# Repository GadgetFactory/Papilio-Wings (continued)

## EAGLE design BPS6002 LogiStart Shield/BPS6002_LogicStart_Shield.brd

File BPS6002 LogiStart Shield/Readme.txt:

BPS6002 LogicStart Shield Manufacturing Package - Current Version 1.02

Special assembly instructions:
	-Use RED for the PCB color.
	-All Arduino Mega Header pins should be populated with Male headers on the bottom of the board.
	-There is a V-Score indicated on the dimension layer of this PCB. The board should be manufactured as a single PCB with both sides of the V-Score connected. The end user will snap away the V-Score if they wish to do so.

Test Plan Home Page:
	http://www.gadgetfactory.net/opmanuals/index.php?n=Main.LogicStartShield

3D Rendering Video:
https://www.youtube.com/watch?v=OsVe8Iz7Yxw
	
CHANGELOG
11/18/2014	Version 1.02
	-Moved the Audio jack out for easier manufacturing.

10/22/2014	Version 1.01
	-R48-R52 were not in the BOM for 1.0, added for 1.01
	-The Seven Segment Display must be a Common Anode type display - the prototypes used Common Cathode which do not work.
	-Changed the Analog voltage from 5V to 3.3V
	-Added AREF access point.

8/12/2014 	Version 1.0
	First release with V-Score.

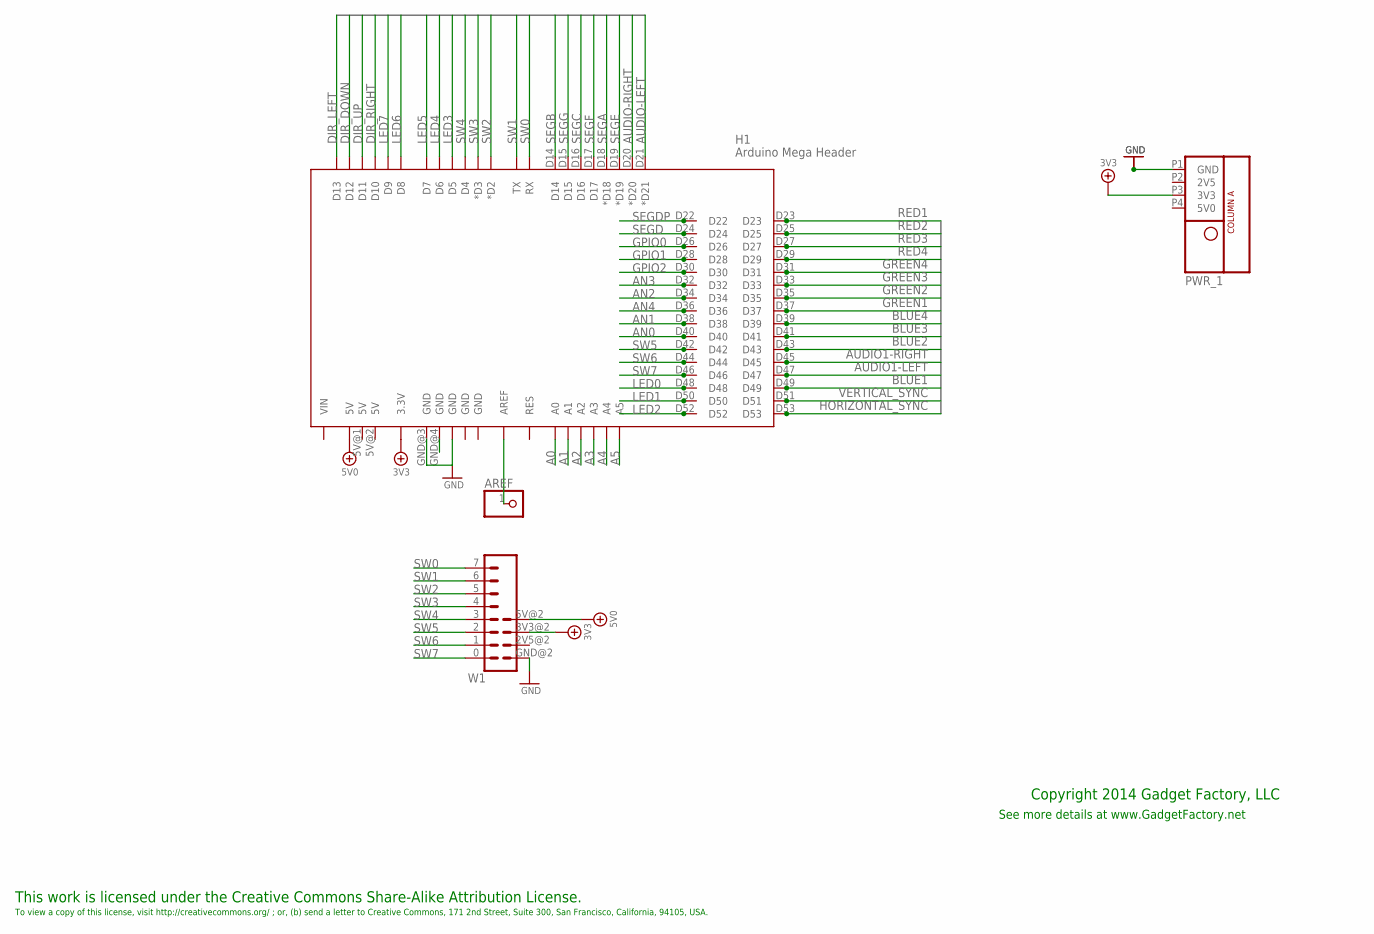
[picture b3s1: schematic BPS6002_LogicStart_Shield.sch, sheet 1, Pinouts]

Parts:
AREF: PINHD-1X1; 1X01
H1: Arduino Mega Header; PAPILIO_DUO_SHIELD; PARTNO 65PinHeader
LOGO1: BUTTERFLY_LOGO
PWR_1: POWER_ONLYNOTEXT; POWER_NO_TEXT
W1: WING8_NOHOLES_FEMALE_TOP; WINGSIDE_8BIT_NOHOLES

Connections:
3V3: H1.3.3V, W1.3V3@2 (3V3); also elsewhere on the board
5V0: H1.5V@0 (5V), W1.5V@2 (5V)
A0: H1.A0; also elsewhere on the board
A1: H1.A1; also elsewhere on the board
A2: H1.A2; also elsewhere on the board
A3: H1.A3; also elsewhere on the board
A4: H1.A4; also elsewhere on the board
A5: H1.A5; also elsewhere on the board
AN0: H1.D40; also elsewhere on the board
AN1: H1.D38; also elsewhere on the board
AN2: H1.D34; also elsewhere on the board
AN3: H1.D32; also elsewhere on the board
AN4: H1.D36; also elsewhere on the board
AUDIO1-LEFT: H1.D47
AUDIO1-RIGHT: H1.D45
AUDIO-LEFT: H1.D21 (*D21); also elsewhere on the board
AUDIO-RIGHT: H1.D20 (*D20); also elsewhere on the board
BLUE1: H1.D49; also elsewhere on the board
BLUE2: H1.D43; also elsewhere on the board
BLUE3: H1.D41; also elsewhere on the board
BLUE4: H1.D39; also elsewhere on the board
DIR_DOWN: H1.D12; also elsewhere on the board
DIR_LEFT: H1.D13; also elsewhere on the board
DIR_RIGHT: H1.D10; also elsewhere on the board
DIR_UP: H1.D11; also elsewhere on the board
GND: H1.GND@2 (GND), H1.GND@3 (GND), W1.GND@2 (GND); also elsewhere on the board
GPIO0: H1.D26; also elsewhere on the board
GPIO1: H1.D28; also elsewhere on the board
GPIO2: H1.D30; also elsewhere on the board
GREEN1: H1.D37; also elsewhere on the board
GREEN2: H1.D35; also elsewhere on the board
GREEN3: H1.D33; also elsewhere on the board
GREEN4: H1.D31; also elsewhere on the board
HORIZONTAL_SYNC: H1.D53; also elsewhere on the board
LED0: H1.D48; also elsewhere on the board
LED1: H1.D50; also elsewhere on the board
LED2: H1.D52; also elsewhere on the board
LED3: H1.D5; also elsewhere on the board
LED4: H1.D6; also elsewhere on the board
LED5: H1.D7; also elsewhere on the board
LED6: H1.D8; also elsewhere on the board
LED7: H1.D9; also elsewhere on the board
unnamed: AREF.1, H1.AREF
RED1: H1.D23; also elsewhere on the board
RED2: H1.D25; also elsewhere on the board
RED3: H1.D27; also elsewhere on the board
RED4: H1.D29; also elsewhere on the board
SEGA: H1.D18 (*D18); also elsewhere on the board
SEGB: H1.D14; also elsewhere on the board
SEGC: H1.D16; also elsewhere on the board
SEGD: H1.D24; also elsewhere on the board
SEGDP: H1.D22; also elsewhere on the board
SEGE: H1.D19 (*D19); also elsewhere on the board
SEGF: H1.D17; also elsewhere on the board
SEGG: H1.D15; also elsewhere on the board
SW0: H1.RX, W1.7 (8); also elsewhere on the board
SW1: H1.TX, W1.6 (7); also elsewhere on the board
SW2: H1.D2 (*D2), W1.5 (6); also elsewhere on the board
SW3: H1.D3 (*D3), W1.4 (5); also elsewhere on the board
SW4: H1.D4, W1.3 (4); also elsewhere on the board
SW5: H1.D42, W1.2 (3); also elsewhere on the board
SW6: H1.D44, W1.1 (2); also elsewhere on the board
SW7: H1.D46, W1.0 (1); also elsewhere on the board
VERTICAL_SYNC: H1.D51; also elsewhere on the board
WING_3V3: PWR_1.P3 (3V3)
WING_GND: H1.GND@4 (GND), PWR_1.P1 (GND); also elsewhere on the board

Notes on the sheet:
This work is licensed under the Creative Commons Share-Alike Attribution License.
To view a copy of this license, visit http://creativecommons.org/ ; or, (b) send a letter to Creative Commons, 171 2nd Street, Suite 300, San Francisco, California, 94105, USA.
Copyright 2014 Gadget Factory, LLC
See more details at www.GadgetFactory.net

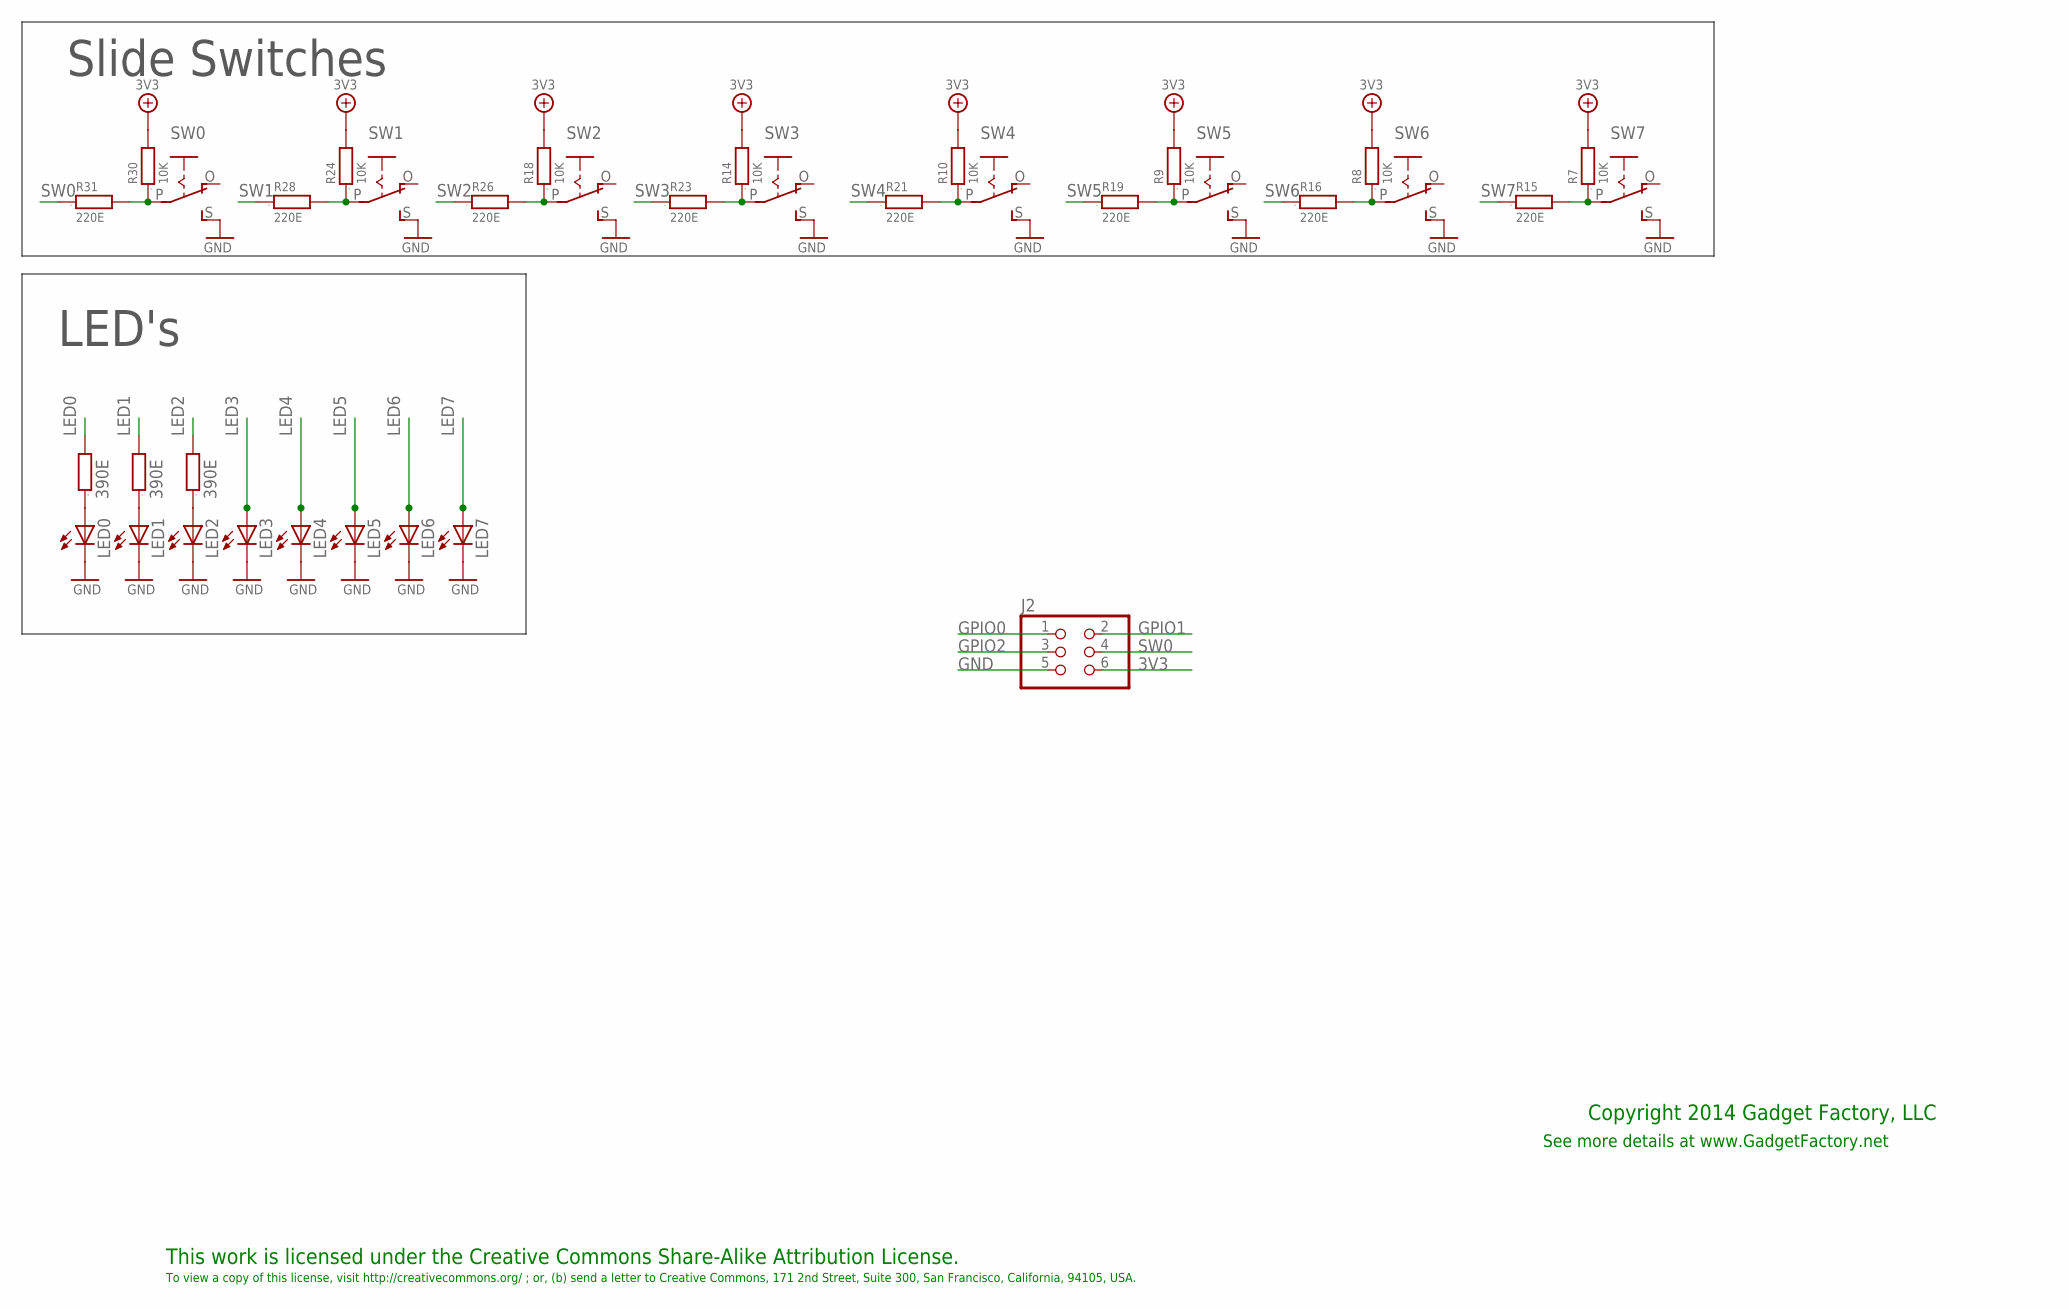
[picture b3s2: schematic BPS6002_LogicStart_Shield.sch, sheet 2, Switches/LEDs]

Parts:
J2: PINHD-2X3; 2X03
LED0, LED1, LED2, LED3, LED4, LED5, LED6, LED7: LEDCHIPLED_0805; CHIPLED_0805; PARTNO LTST-C170KGKT
R7, R8, R9, R10, R14, R18, R24, R30: 10K; 0603; PARTNO RMCF0603JT10K0
R11, R12, R13: 390E; 0603; PARTNO RMCF0603JT390R
R15, R16, R19, R21, R23, R26, R28, R31: 220E; 0603; PARTNO RMCF0603JT220R
SW0, SW1, SW2, SW3, SW4, SW5, SW6, SW7: EG1218S; EG1218; PARTNO EG1218

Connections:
3V3: J2.6, R7.2, R8.2, R9.2, R10.2, R14.2, R18.2, R24.2, R30.2; also elsewhere on the board
GND: J2.5, LED0.C, LED1.C, LED2.C, LED3.C, LED4.C, LED5.C, LED6.C, LED7.C, SW0.S, SW1.S, SW2.S, SW3.S, SW4.S, SW5.S, SW6.S, SW7.S; also elsewhere on the board
GPIO0: J2.1; also elsewhere on the board
GPIO1: J2.2; also elsewhere on the board
GPIO2: J2.3; also elsewhere on the board
LED0: R13.2; also elsewhere on the board
LED1: R12.2; also elsewhere on the board
LED2: R11.2; also elsewhere on the board
LED3: LED3.A; also elsewhere on the board
LED4: LED4.A; also elsewhere on the board
LED5: LED5.A; also elsewhere on the board
LED6: LED6.A; also elsewhere on the board
LED7: LED7.A; also elsewhere on the board
unnamed: LED0.A, R13.1
unnamed: LED1.A, R12.1
unnamed: LED2.A, R11.1
SW0: J2.4, R31.1; also elsewhere on the board
SW0_JOY_UP_IN: R30.1, R31.2, SW0.P
SW1: R28.1; also elsewhere on the board
SW1__JOY_DOWN_IN: R24.1, R28.2, SW1.P
SW2: R26.1; also elsewhere on the board
SW2_JOY_SELECT_IN: R18.1, R26.2, SW2.P
SW3: R23.1; also elsewhere on the board
SW3_JOY_RIGHT_IN: R14.1, R23.2, SW3.P
SW4: R21.1; also elsewhere on the board
SW4_JOY_LEFT_IN: R10.1, R21.2, SW4.P
SW5: R19.1; also elsewhere on the board
SW5_IN: R9.1, R19.2, SW5.P
SW6: R16.1; also elsewhere on the board
SW6_IN: R8.1, R16.2, SW6.P
SW7: R15.1; also elsewhere on the board
SW7_IN: R7.1, R15.2, SW7.P

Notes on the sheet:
This work is licensed under the Creative Commons Share-Alike Attribution License.
To view a copy of this license, visit http://creativecommons.org/ ; or, (b) send a letter to Creative Commons, 171 2nd Street, Suite 300, San Francisco, California, 94105, USA.
Copyright 2014 Gadget Factory, LLC
See more details at www.GadgetFactory.net
LED's
Slide Switches

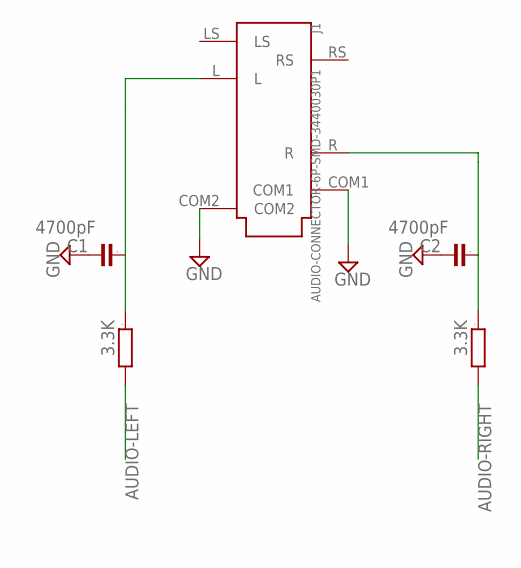
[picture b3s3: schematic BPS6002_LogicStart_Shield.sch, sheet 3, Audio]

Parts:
C1, C2: 4700pF; 0603; PARTNO C0603C472J5RACTU
J1: AUDIO-CONNECTOR-6P-SMD-3440030P1; 6P-SMD-3.5; PARTNO 3440030P1
R2, R3: 3.3K; 0603; PARTNO RMCF0603JT3K30

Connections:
AUDIO-LEFT: R2.2; also elsewhere on the board
AUDIO-RIGHT: R3.2; also elsewhere on the board
GND: C1.2, C2.2, J1.COM1, J1.COM2; also elsewhere on the board
unnamed: C1.1, J1.L, R2.1
unnamed: C2.1, J1.R, R3.1

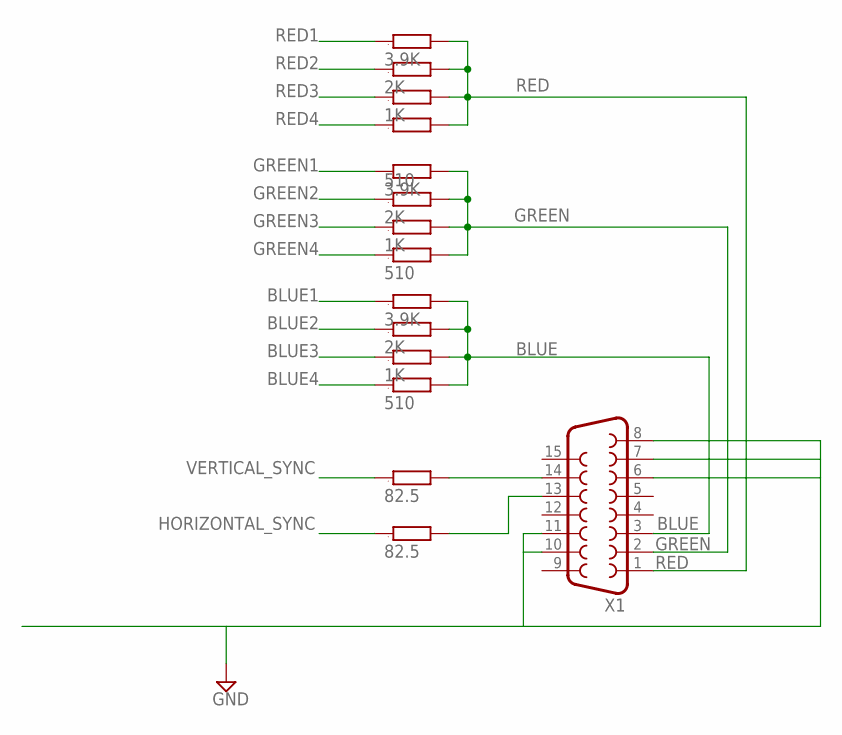
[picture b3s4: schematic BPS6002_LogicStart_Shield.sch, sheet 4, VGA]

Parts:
R34, R41, R45: 3.9K; 0603; PARTNO RMCF0603JT3K90
R35, R40, R44: 2K; 0603; PARTNO RMCF0603JT2K00
R36, R39, R43: 1K; 0603; PARTNO RMCF0603JT1K00
R37, R38, R42: 510; 0603; PARTNO RMCF0603JT510R
R46, R47: 82.5; 0603; PARTNO RMCF0603FT82R5
X1: F15HDH; HDF15H; PARTNO 1-1734530-1

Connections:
BLUE: R42.2, R43.2, R44.2, R45.2, X1.3
BLUE1: R45.1; also elsewhere on the board
BLUE2: R44.1; also elsewhere on the board
BLUE3: R43.1; also elsewhere on the board
BLUE4: R42.1; also elsewhere on the board
GREEN: R38.2, R39.2, R40.2, R41.2, X1.2
GREEN1: R41.1; also elsewhere on the board
GREEN2: R40.1; also elsewhere on the board
GREEN3: R39.1; also elsewhere on the board
GREEN4: R38.1; also elsewhere on the board
HORIZONTAL_SYNC: R47.1; also elsewhere on the board
unnamed: R47.2, X1.13
unnamed: R46.2, X1.14
RED: R34.2, R35.2, R36.2, R37.2, X1.1
RED1: R34.1; also elsewhere on the board
RED2: R35.1; also elsewhere on the board
RED3: R36.1; also elsewhere on the board
RED4: R37.1; also elsewhere on the board
VERTICAL_SYNC: R46.1; also elsewhere on the board
WING_GND: X1.6, X1.7, X1.8, X1.10, X1.11; also elsewhere on the board

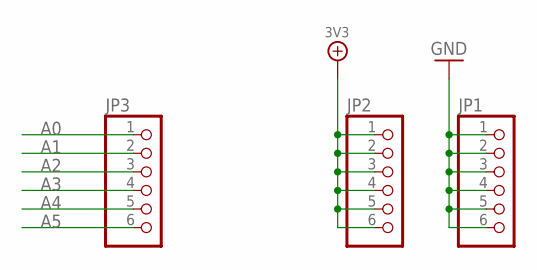
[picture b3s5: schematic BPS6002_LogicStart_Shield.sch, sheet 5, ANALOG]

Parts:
JP1, JP2, JP3: PINHD-1X6; 1X06; PARTNO 68000-406HLF

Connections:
3V3: JP2.1, JP2.2, JP2.3, JP2.4, JP2.5, JP2.6; also elsewhere on the board
A0: JP3.1; also elsewhere on the board
A1: JP3.2; also elsewhere on the board
A2: JP3.3; also elsewhere on the board
A3: JP3.4; also elsewhere on the board
A4: JP3.5; also elsewhere on the board
A5: JP3.6; also elsewhere on the board
GND: JP1.1, JP1.2, JP1.3, JP1.4, JP1.5, JP1.6; also elsewhere on the board

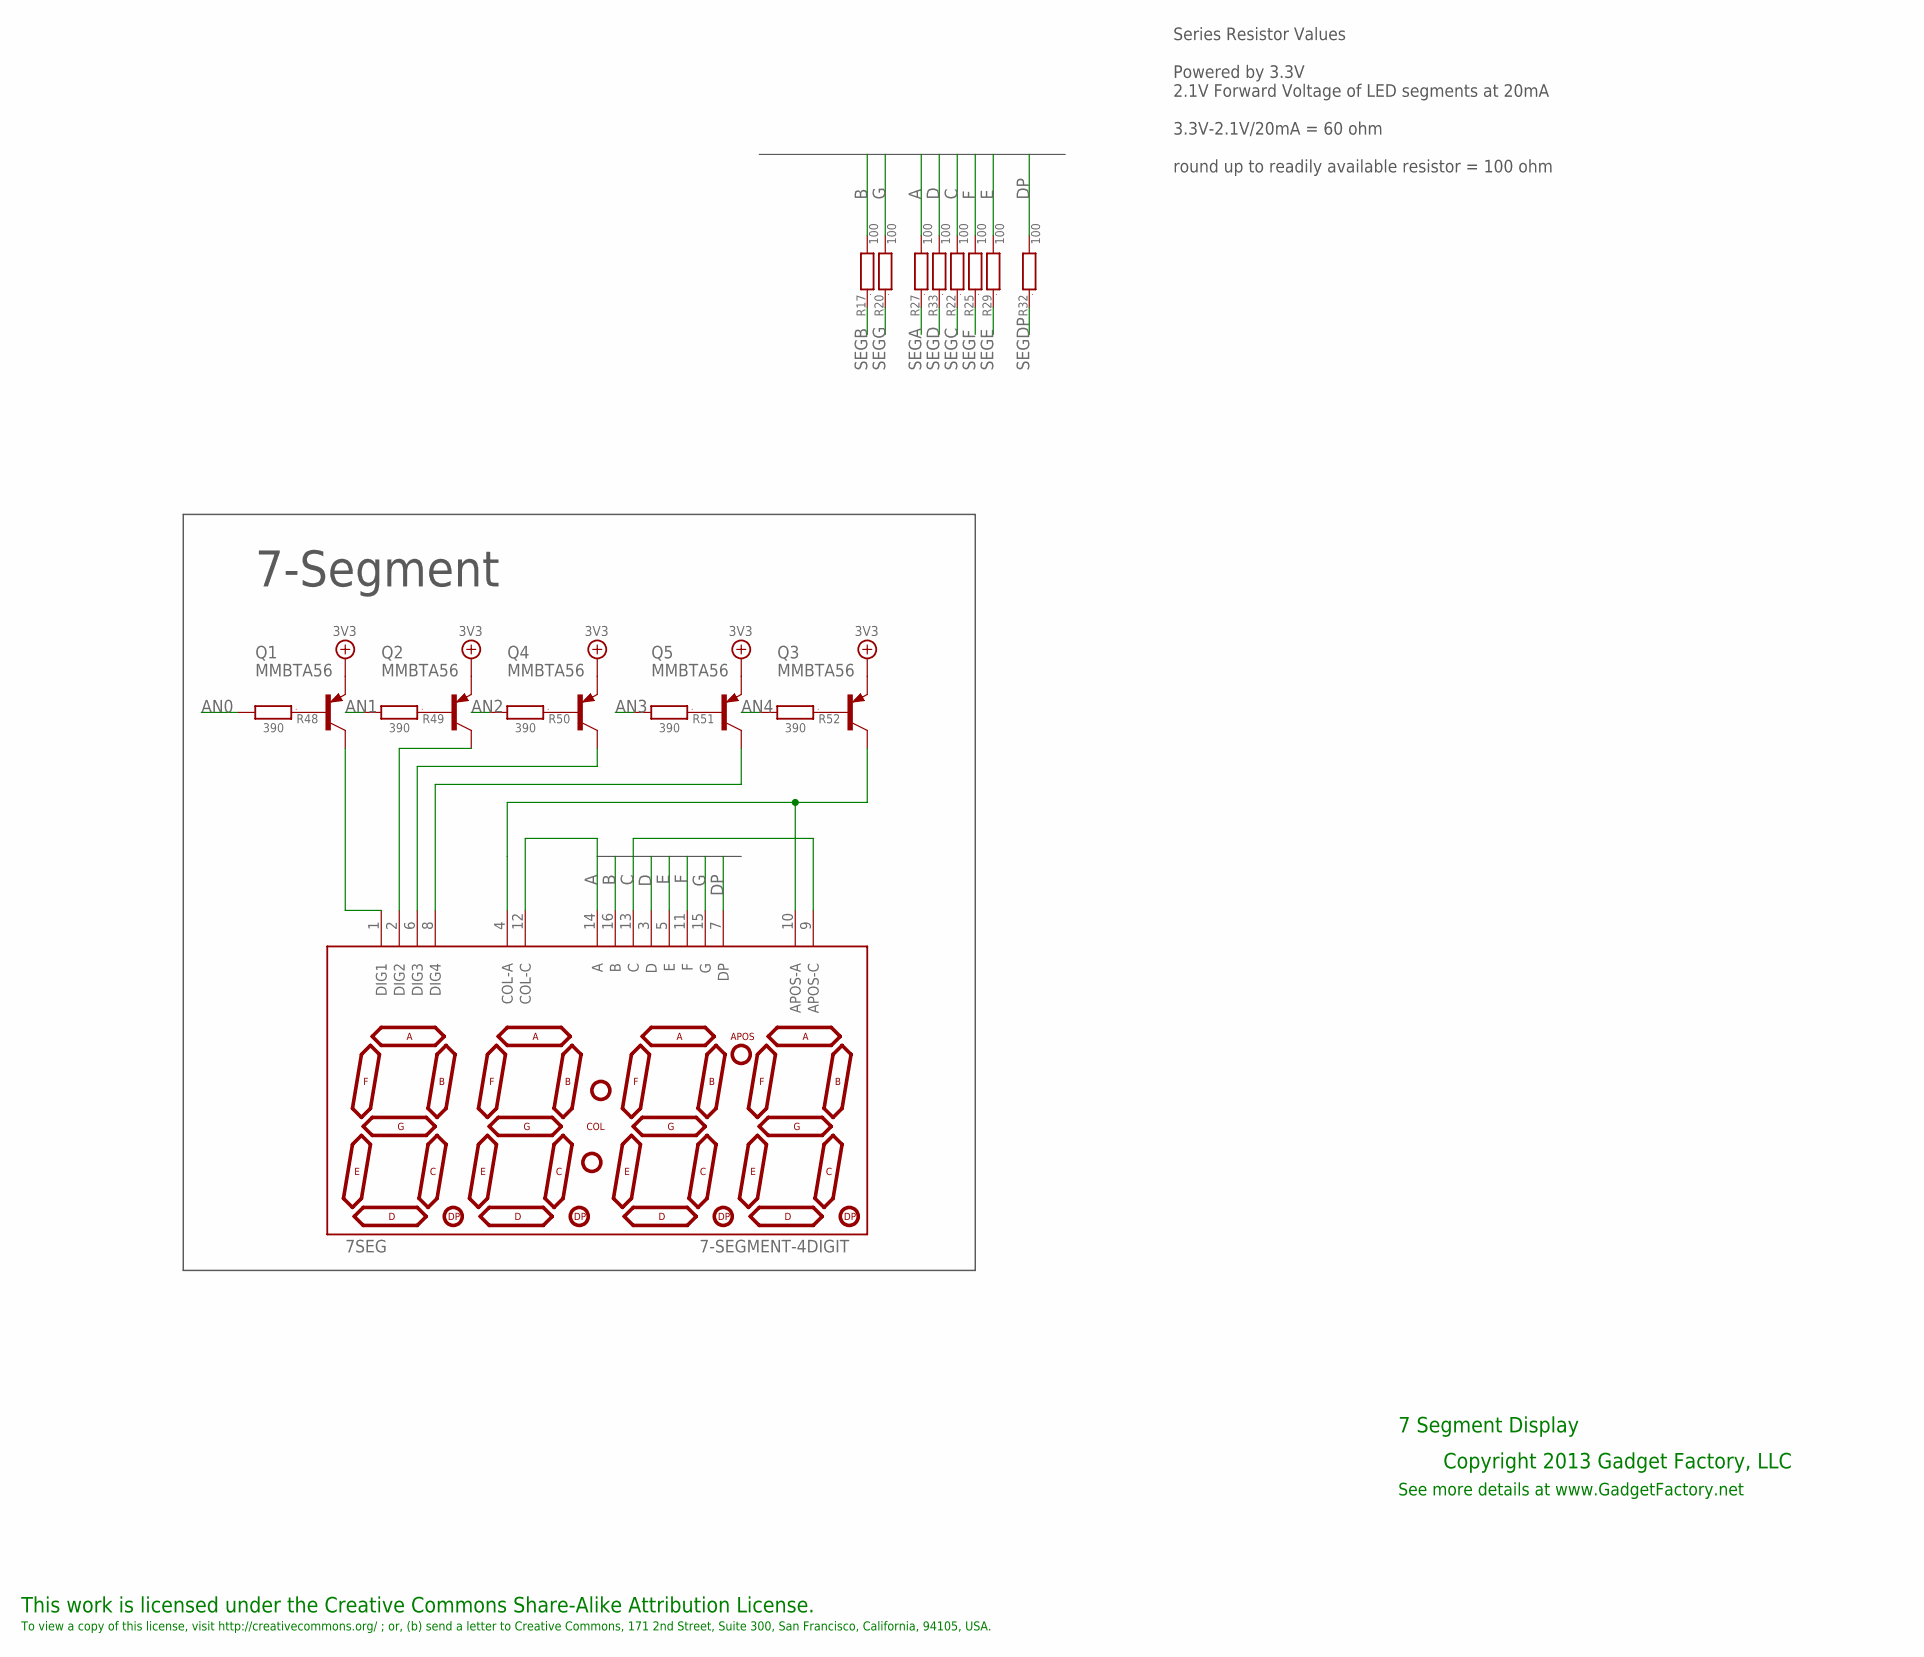
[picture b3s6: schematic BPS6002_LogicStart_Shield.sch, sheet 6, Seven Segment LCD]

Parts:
7SEG: 7-SEGMENT-4DIGIT; PARTNO AL-D4012BWSR/58-040C
Q1, Q2, Q3, Q4, Q5: MMBTA56; SOT23; PARTNO MMBTA56
R17, R20, R22, R25, R27, R29, R32, R33: 100; 0603; PARTNO CRCW0603100RJNEA
R48, R49, R50, R51, R52: 390; 0603; PARTNO CRCW0603100RJNEA

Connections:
3V3: Q1.2 (E), Q2.2 (E), Q3.2 (E), Q4.2 (E), Q5.2 (E); also elsewhere on the board
A: 7SEG.12 (COL-C), 7SEG.14 (A), R27.2
AN0: R48.2; also elsewhere on the board
AN1: R49.2; also elsewhere on the board
AN2: R50.2; also elsewhere on the board
AN3: R51.2; also elsewhere on the board
AN4: R52.2; also elsewhere on the board
APOS_A: 7SEG.4 (COL-A), 7SEG.10 (APOS-A), Q3.3 (C)
B: 7SEG.16 (B), R17.2
C: 7SEG.9 (APOS-C), 7SEG.13 (C), R22.2
D: 7SEG.3 (D), R33.2
DP: 7SEG.7 (DP), R32.2
E: 7SEG.5 (E), R29.2
F: 7SEG.11 (F), R25.2
G: 7SEG.15 (G), R20.2
unnamed: Q1.1 (B), R48.1
unnamed: Q2.1 (B), R49.1
unnamed: Q4.1 (B), R50.1
unnamed: Q5.1 (B), R51.1
unnamed: Q3.1 (B), R52.1
unnamed: 7SEG.1 (DIG1), Q1.3 (C)
unnamed: 7SEG.2 (DIG2), Q2.3 (C)
unnamed: 7SEG.6 (DIG3), Q4.3 (C)
unnamed: 7SEG.8 (DIG4), Q5.3 (C)
SEGA: R27.1; also elsewhere on the board
SEGB: R17.1; also elsewhere on the board
SEGC: R22.1; also elsewhere on the board
SEGD: R33.1; also elsewhere on the board
SEGDP: R32.1; also elsewhere on the board
SEGE: R29.1; also elsewhere on the board
SEGF: R25.1; also elsewhere on the board
SEGG: R20.1; also elsewhere on the board

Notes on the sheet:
This work is licensed under the Creative Commons Share-Alike Attribution License.
To view a copy of this license, visit http://creativecommons.org/ ; or, (b) send a letter to Creative Commons, 171 2nd Street, Suite 300, San Francisco, California, 94105, USA.
Copyright 2013 Gadget Factory, LLC
See more details at www.GadgetFactory.net
7-Segment
7 Segment Display
Series Resistor Values Powered by 3.3V 2.1V Forward Voltage of LED segments at 20mA 3.3V-2.1V/20mA = 60 ohm round up to readily available resistor = 100 ohm

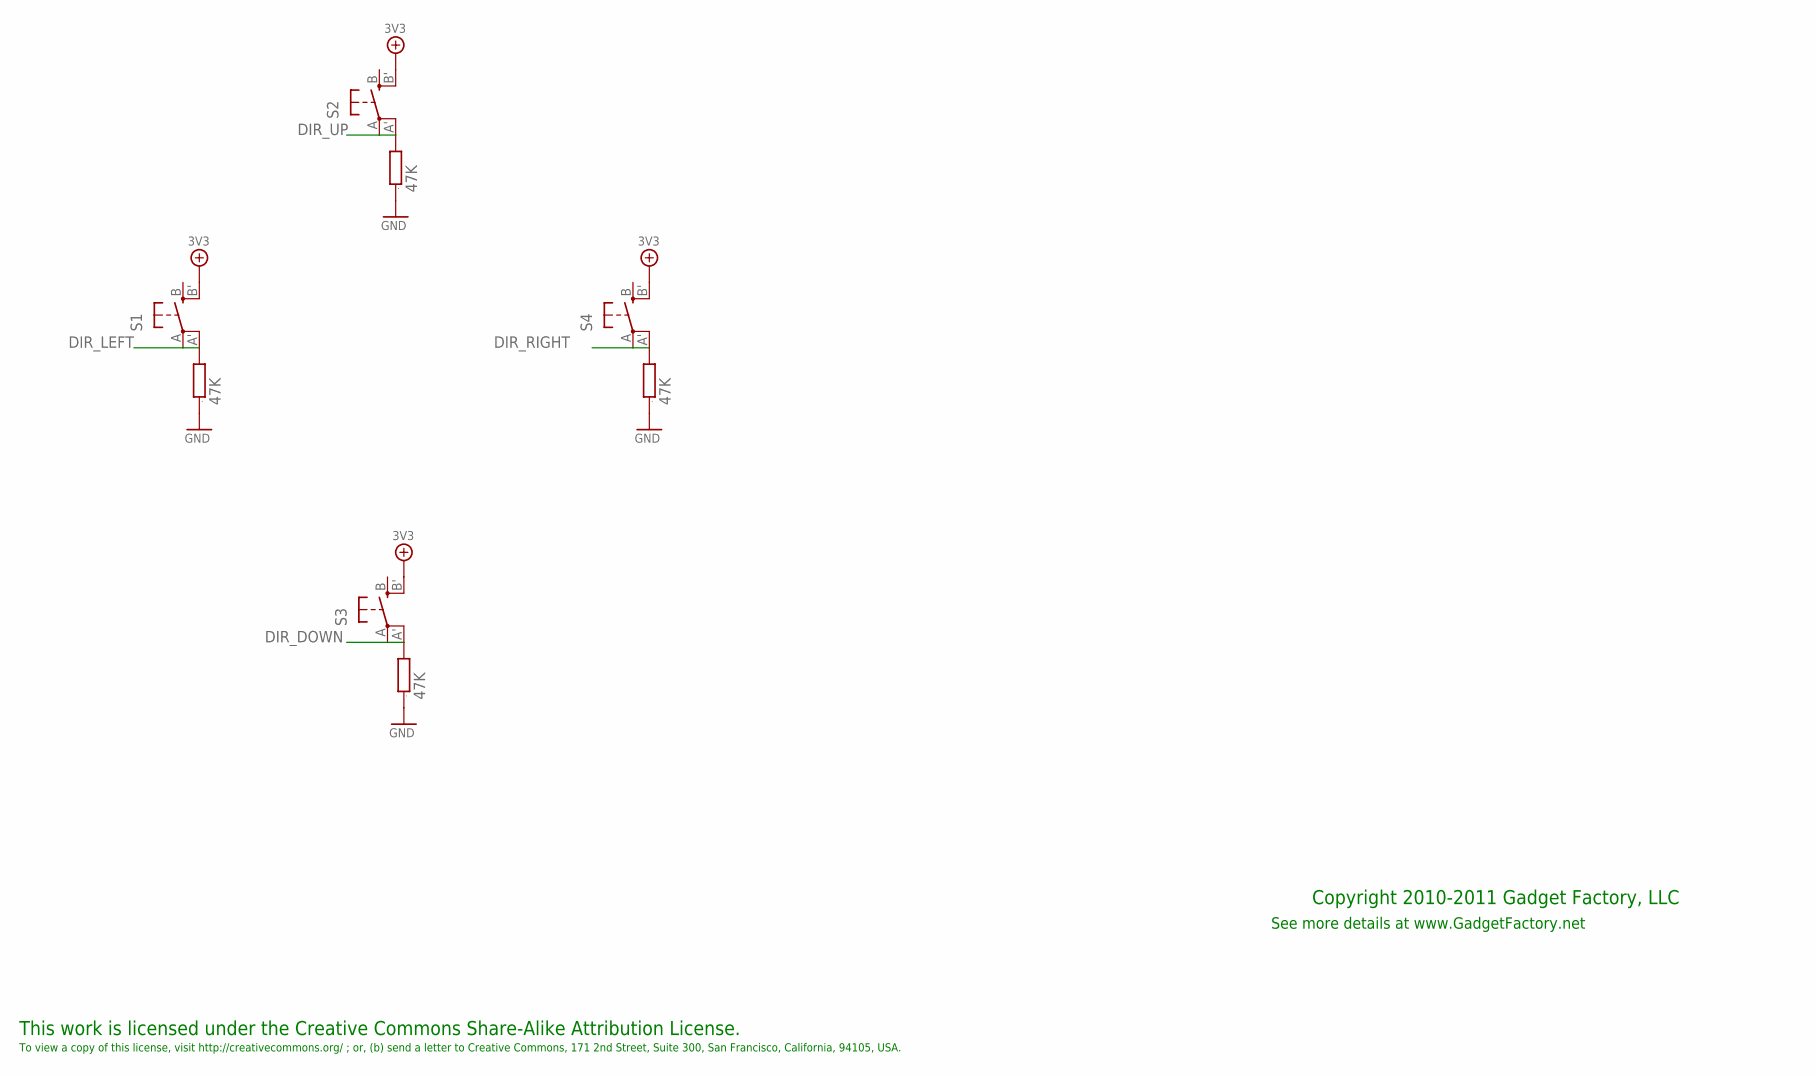
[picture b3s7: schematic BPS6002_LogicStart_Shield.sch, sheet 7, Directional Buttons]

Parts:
R1, R4, R5, R6: 47K; 0603; PARTNO RMCF0603JT47K0
S1, S2, S3, S4: EVQQ2; EVQ-Q2; PARTNO PTS525SM10SMTR LFS

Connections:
3V3: S1.B' (S1), S2.B' (S1), S3.B' (S1), S4.B' (S1); also elsewhere on the board
DIR_DOWN: R4.2, S3.A, S3.A' (P1); also elsewhere on the board
DIR_LEFT: R1.2, S1.A, S1.A' (P1); also elsewhere on the board
DIR_RIGHT: R6.2, S4.A, S4.A' (P1); also elsewhere on the board
DIR_UP: R5.2, S2.A, S2.A' (P1); also elsewhere on the board
GND: R1.1, R4.1, R5.1, R6.1; also elsewhere on the board

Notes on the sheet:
This work is licensed under the Creative Commons Share-Alike Attribution License.
To view a copy of this license, visit http://creativecommons.org/ ; or, (b) send a letter to Creative Commons, 171 2nd Street, Suite 300, San Francisco, California, 94105, USA.
Copyright 2010-2011 Gadget Factory, LLC
See more details at www.GadgetFactory.net

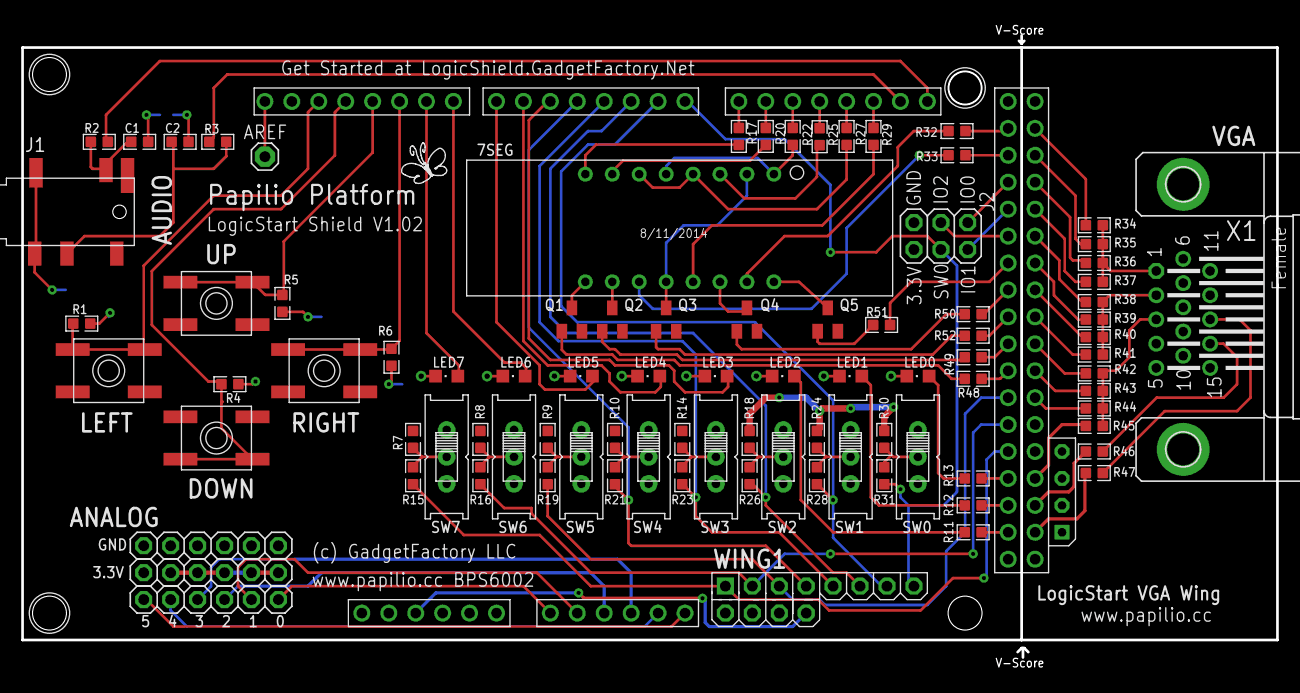
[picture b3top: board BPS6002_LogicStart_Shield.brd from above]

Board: 2 copper layers, 118.4 x 61.1 mm, 92 parts (0 on the bottom side), 99 nets.

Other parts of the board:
U$1: STAND-OFF-TIGHT

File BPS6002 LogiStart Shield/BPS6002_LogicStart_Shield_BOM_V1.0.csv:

Qty-1,Part References,Value,Package,Mfg Part Num,Mfg Name,VID,Vendor Part Num,Description,Pkg Code,,XREF
1,"X1",,HDF15H,1-1734530-1,TE Connectivity,DK,A35116-ND,CONN HD D-SUB RCPT R/A 15POS - VGA Connector,*,*,REF182
3,"JP1, JP2, JP3",,1X06,68000-406HLF,FCI,DK,609-3263-ND,6 Pin Male Header,1X06,*,REF190
8,"SW0, SW1, SW2, SW3, SW4, SW5, SW6, SW7",,EG1218,EG1218,E-Switch,DK,EG1903-ND,SWITCH SLIDE SPDT 30V.2A PC MNT - Used in Logicstart,EG1218,*,REF187
8,"LED0, LED1, LED2, LED3, LED4, LED5, LED6, LED7",,CHIPLED_0805,LTST-C170KGKT,LITE-ON INC (VA),DK,160-1414-1-ND,LED GREEN CLEAR 0805 SMD,805,*,REF111
4,"S1, S2, S3, S4",,EVQ-Q2,PTS525SM10SMTR LFS,C&K Components,DK,CKN9104CT-ND,SWITCH TACTILE SPST-NO 0.05A 12V,*,*,REF119
3,"R36, R39, R43",1K,0603,RMCF0603JT1K00,StackPole,DK,RMCF0603JT1K00CT-ND,RES 1K OHM 1/10W 5% 0603,603,*,REF140
3,"R35, R40, R44",2K,0603,RMCF0603JT2K00,Stackpole,DK,RMCF0603JT2K00CT-ND,RES 2K OHM 1/10W 5% 0603,603,*,REF172
2,"R2, R3",3.3K,0603,RMCF0603JT3K30,Stackpole,DK,RMCF0603JT3K30CT-ND,RES 3.3K OHM 1/10W 5% 0603,603,*,REF168
3,"R34, R41, R45",3.9K,0603,RMCF0603JT3K90,Stackpole,DK,RMCF0603JT3K90CT-ND,RES 3.9K OHM 1/10W 5% 0603,603,*,REF171
1,"7SEG",7-SEGMENT-4DIGIT,7-SEGMENT-4DIGIT,AL-D4012BWSR/58-040C,China Young Sun LED,SP,COM-09483,Sparkfun - Seven Segment Display - Used in LogicStart,7-SEGMENT-4DIGIT,*,REF189
8,"R7, R8, R9, R10, R14, R18, R24, R30",10K,0603,RMCF0603JT10K0,StackPole,DK,RMCF0603JT10K0CT-ND,RES 10K OHM 1/10W 5% 0603,603,*,REF142
4,"R1, R4, R5, R6",47K,0603,RMCF0603JT47K0,Stackpole,DK,RMCF0603JT47K0CT-ND,RES 47K OHM 1/10W 5% 0603,603,*,REF167
2,"R46, R47",82.5,0603,RMCF0603FT82R5,Stackpole,DK,RMCF0603FT82R5CT-ND,RES 82.5 OHM 1/10W 1% 0603,603,*,REF170
8,"R17, R20, R22, R25, R27, R29, R32, R33",100,0603,CRCW0603100RJNEA,VISHAY DALE (VA),DK,541-100GCT-ND,RES 100 OHM 1/10W 5% 0603 SMD,603,*,REF192
8,"R15, R16, R19, R21, R23, R26, R28, R31",220E,0603,RMCF0603JT220R,Stackpole,DK,RMCF0603JT220RCT-ND,RES 220 OHM 1/10W 5% 0603,603,*,REF186
3,"R11, R12, R13",390E,0603,RMCF0603JT390R,StackPole,DK,RMCF0603JT390RCT-ND,RES 390 OHM 1/10W 5% 0603,603,*,REF141
3,"R37, R38, R42",510,0603,RMCF0603JT510R,Stackpole,DK,RMCF0603JT510RCT-ND,RES 510 OHM 1/10W 5% 0603,603,*,REF174
2,"C1, C2",4700pF,0603,C0603C472J5RACTU,Kemet,DK,399-1088-1-ND,CAP CER 4700PF 50V 5% X7R 0603 - Audio cap,603,*,REF175
1,"J1",AUDIO-CONNECTOR-6P-SMD-3440030P1,6P-SMD-3.5,3440030P1,Seeed Studio,SD,3440030P1,6P-SMD-3.5 - Audio Connector,*,*,REF183
1,"H1",Arduino Mega Header,PAPILIO_DUO_SHIELD,65PinHeader,Generic,GN,65PinHeader,1x65 Male Pin Header .1 inch - To be broken up for Arduino Header,*,*,REF185
5,"Q1, Q2, Q3, Q4, Q5",MMBTA56,SOT23,MMBTA56,Fairfield Semiconductor,DK,MMBTA56FSCT-ND,TRANSISTOR GP PNP AMP SOT-23 - For 7 Seg Display,SOT23,*,REF191

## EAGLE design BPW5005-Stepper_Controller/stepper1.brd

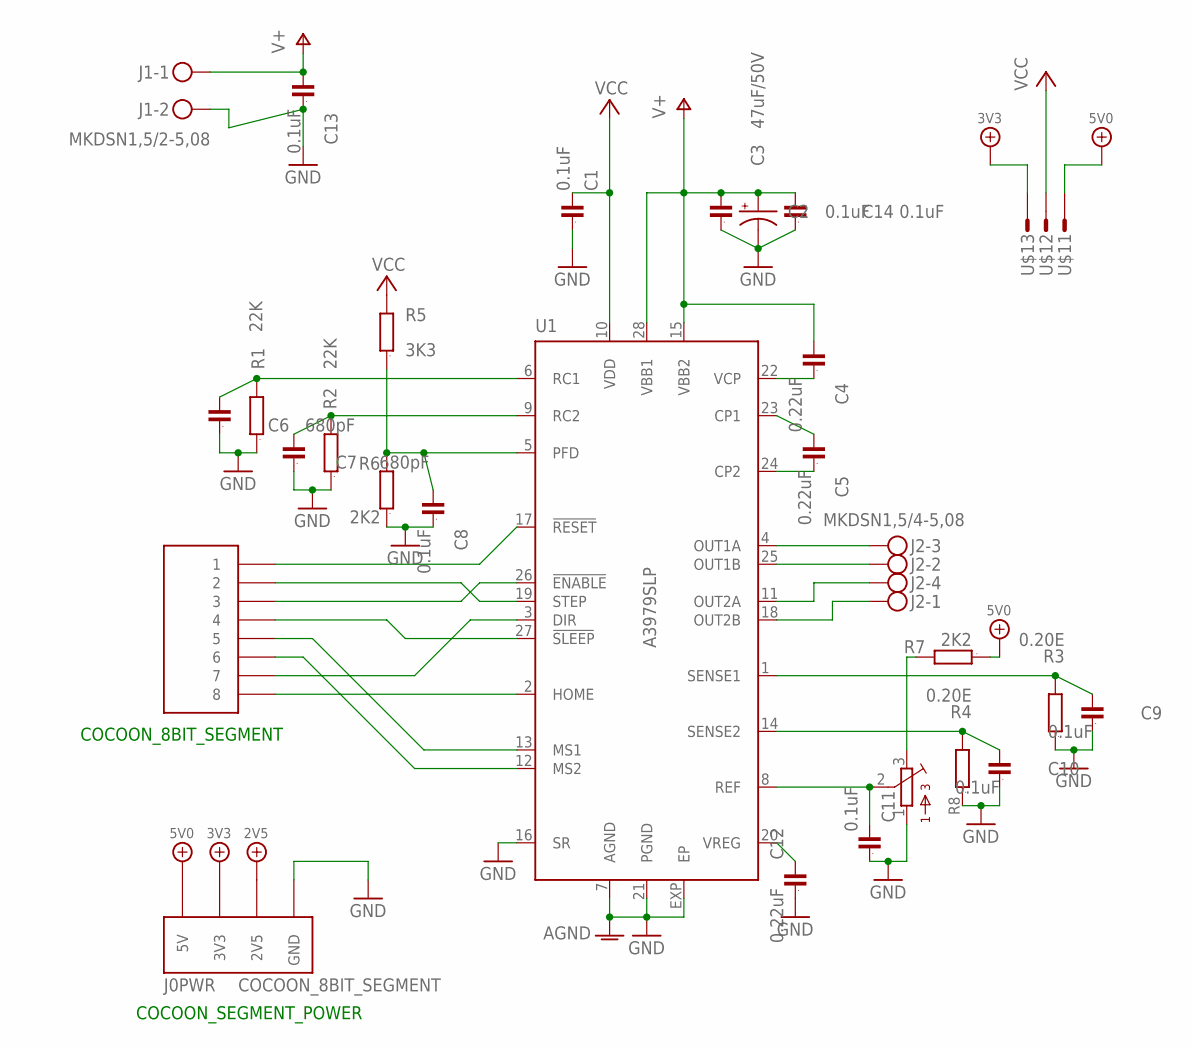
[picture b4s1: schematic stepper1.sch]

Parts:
C1, C8, C11: 0.1uF; 0603
C2, C9, C10, C13, C14: 0.1uF; 0805
C3: 47uF/50V; E2,5-7
C4, C5, C12: 0.22uF; 0805
C6, C7: 680pF; 0603
J0: COCOON_8BIT_SEGMENT
J1: MKDSN1,5/2-5,08
J2: MKDSN1,5/4-5,08
LOGO1: BUTTERFLY_LOGO
R1, R2: 22K; 0603
R3, R4: 0.20E; 2512
R5: 3K3; 0603
R6, R7: 2K2; 0603
R8: 3386-P; 3386P
U1: A3979SLP; TSSOP28
U$1: JPS3X1; JP3X1

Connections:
2V5: J0.2V5
3V3: J0.3V3, U$1.3
5V0: J0.5V, R7.1, U$1.1
GND: C1.1, C2.1, C3.-, C6.1, C7.1, C8.1, C9.1, C10.1, C11.1, C12.1, C13.1, C14.1, J0.GND, J1.2, R1.1, R2.1, R3.1, R4.1, R6.1, R8.1, U1.7 (AGND), U1.16 (SR), U1.21 (PGND), U1.EXP (EP)
unnamed: R7.2, R8.3
unnamed: C6.2, R1.2, U1.6 (RC1)
unnamed: C7.2, R2.2, U1.9 (RC2)
unnamed: J0.6, U1.12 (MS2)
unnamed: C4.1, U1.22 (VCP)
unnamed: J0.4, U1.27 (!SLEEP)
unnamed: C11.2, R8.2, U1.8 (REF)
unnamed: C9.2, R3.2, U1.1 (SENSE1)
unnamed: C10.2, R4.2, U1.14 (SENSE2)
unnamed: C12.2, U1.20 (VREG)
unnamed: J0.3, U1.26 (!ENABLE)
unnamed: J0.2, U1.19 (STEP)
unnamed: J0.1, U1.17 (!RESET)
unnamed: C5.1, U1.24 (CP2)
unnamed: C5.2, U1.23 (CP1)
unnamed: J0.8, U1.2 (HOME)
unnamed: J0.5, U1.13 (MS1)
unnamed: J0.7, U1.3 (DIR)
unnamed: C8.2, R5.1, R6.2, U1.5 (PFD)
OUT1A: J2.3, U1.4 (OUT1A)
OUT1B: J2.2, U1.25 (OUT1B)
OUT2A: J2.4, U1.11 (OUT2A)
OUT2B: J2.1, U1.18 (OUT2B)
V+: C2.2, C3.+, C4.2, C13.2, C14.2, J1.1, U1.15 (VBB2), U1.28 (VBB1)
VCC: C1.2, R5.2, U1.10 (VDD), U$1.2

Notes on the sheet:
COCOON_8BIT_SEGMENT
COCOON_SEGMENT_POWER

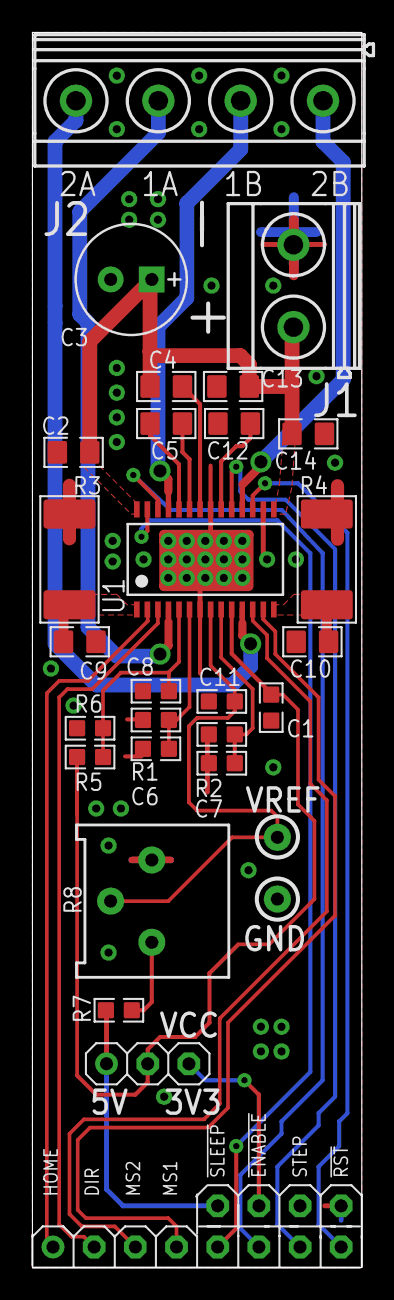
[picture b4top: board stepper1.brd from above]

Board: 2 copper layers, 20.3 x 76.2 mm, 28 parts (1 on the bottom side), 28 nets.
